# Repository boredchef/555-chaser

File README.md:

# 555-chaser
I made this heart shaped led chaser PCB from the start project tutorial on Stasis. How it works is that it uses 2 different ICs which is the 555 timer and the 4017 IC. The 555 component basically is the brains to make the leds blink on and off using astable mode which produces an signal that swithces from on and off. Since we are using a lot of LEDs there is not enough pins on the 555 timer to wire them all so that is why we use the 4017 IC which has the pins. 

This PCB when connected to power and when the potentiometer is turned to let power through the components which then tell the leds to turn on and off. I used this starter project since I thought it would be really fun to learn how to design pcbs using software instead of having to wire things individually on a breadboard and be able to see something from CAD software come to life in hardware which is pretty sick, I also added hearts to gift to someone special :) 

above is the 3D view of the PCB but it does not render the potentiometer or the 4017 IC 

Finished PCB Front

Finished PCB Back

## BoM

| Name | Purpose | Qty | Total | Link | Distributor | 
| --- | --- | --- | --- | --- | --- |
| blinky board kit | leds, ICs, resistors, potentiometer | 1 | $10 | - | HackClub
| custom pcb | the actual design itself with copper plates | 5 | $5.30 | https://jlcpcb.com/ | JLCPCB

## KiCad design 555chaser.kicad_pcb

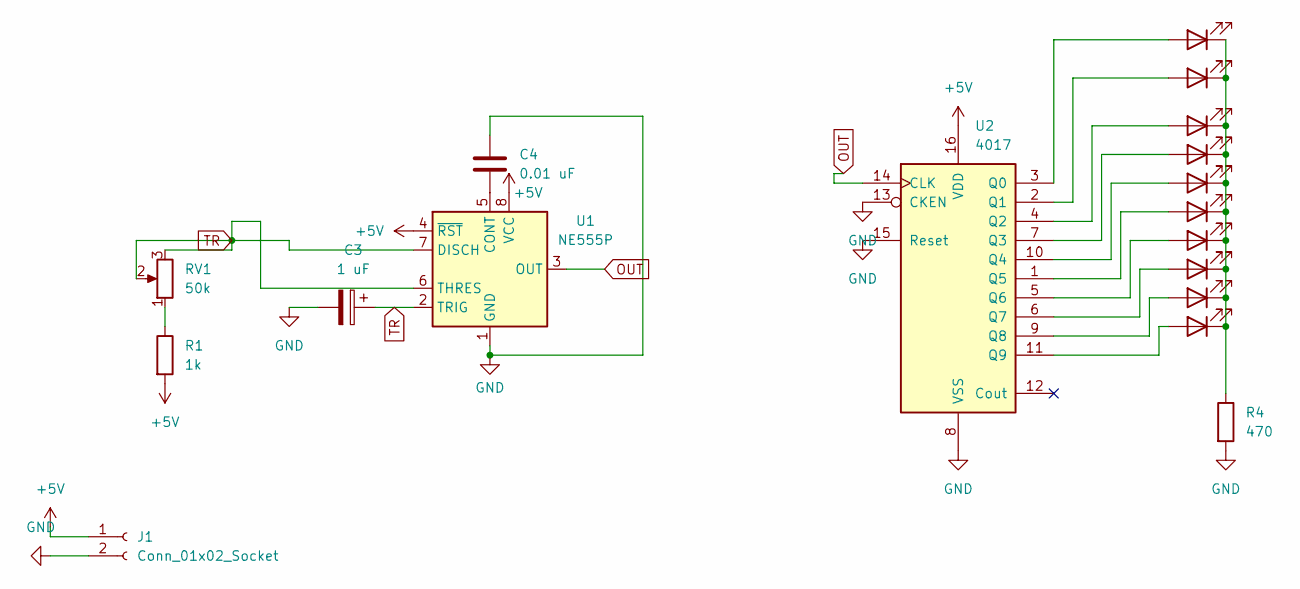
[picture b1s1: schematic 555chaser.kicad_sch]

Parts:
C3: 1 uF; CP_Radial_D5.0mm_P2.00mm
C4: 0.01 uF; C_Disc_D7.5mm_W2.5mm_P5.00mm
D1, D2, D5, D6, D7, D8, D9, D10, D11, D12: LED; LED_D3.0mm
J1: Conn_01x02_Socket; PinHeader_1x02_P2.54mm_Vertical
R1: 1k; R_Axial_DIN0207_L6.3mm_D2.5mm_P7.62mm_Horizontal
R4: 470; R_Axial_DIN0207_L6.3mm_D2.5mm_P7.62mm_Horizontal
RV1: 50k; Potentiometer_Vishay_T93YA_Vertical
U1: NE555P; DIP-8_W7.62mm
U2: 4017; N16

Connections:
+5V: J1.1, R1.2, U1.4 (~RST), U1.8 (VCC), U2.16 (VDD)
GND: C3.2, C4.1, J1.2, R4.2, U1.1 (GND), U2.8 (VSS), U2.13 (CKEN), U2.15 (Reset)
unnamed: D1.2 (A), U2.11 (Q9)
unnamed: D1.1 (K), D2.1 (K), D5.1 (K), D6.1 (K), D7.1 (K), D8.1 (K), D9.1 (K), D10.1 (K), D11.1 (K), D12.1 (K), R4.1
unnamed: D2.2 (A), U2.5 (Q6)
unnamed: D5.2 (A), U2.9 (Q8)
unnamed: D6.2 (A), U2.6 (Q7)
unnamed: D7.2 (A), U2.1 (Q5)
unnamed: D8.2 (A), U2.10 (Q4)
unnamed: D9.2 (A), U2.7 (Q3)
unnamed: D10.2 (A), U2.4 (Q2)
unnamed: D11.2 (A), U2.2 (Q1)
unnamed: D12.2 (A), U2.3 (Q0)
unnamed: R1.1, RV1.1
unnamed: C4.2, U1.5 (CONT)
OUT: U1.3 (OUT), U2.14 (CLK)
TR: C3.1, RV1.2, RV1.3, U1.2 (TRIG), U1.6 (THRES), U1.7 (DISCH)

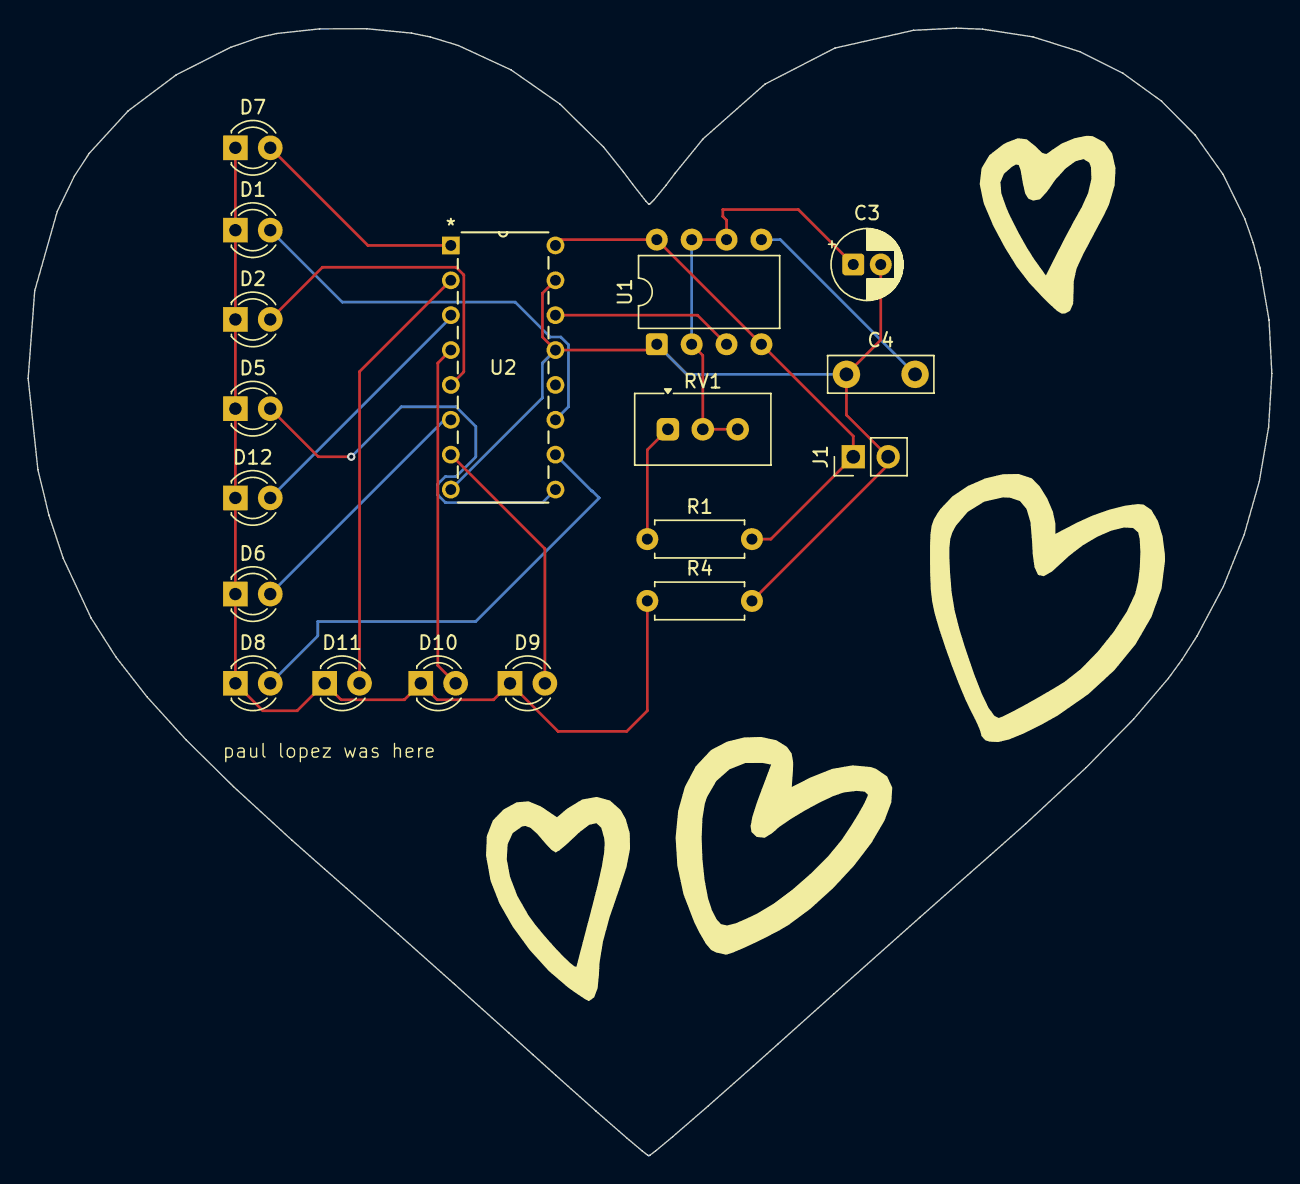
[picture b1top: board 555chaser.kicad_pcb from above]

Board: 2 copper layers, 90.6 x 82.1 mm, 18 parts (0 on the bottom side), 17 nets.

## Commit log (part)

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2026-05-15 Create BoM.csv
    bill of materials for the pcb order
